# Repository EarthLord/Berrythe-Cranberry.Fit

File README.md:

# Berrythe

## Objective

Create a low-cost alternative for a breathing assistant toy in India by replacing the circuitry of a night light toy. The working is similar these toys in these Amazon US [shopping link 1](https://a.co/d/hcPQM95), [shopping link 2](https://a.co/d/2bBX1N4). Below is a video of the resulting breathing sequence from a retrofit night light toy.

https://github.com/user-attachments/assets/268d343a-7a08-4612-9922-748c09accf75

This open-source project is done for [Cranberry.fit](https://cranberry.fit), a company developing personalized care products to improve menstrual health.

## Repository Content

This repository contains both the hardware and firmware for Berrythe - KiCad PCB design and TI Code Composer Studio Project. The respective hardware and firmware folders contain their documentation as well.

## Specifications of toy

1. Overall, the two functional modes are
    1. Breathing mode of 4, 7, 8
    2. Yellow night light mode
2. This needs to be compatible with the toys below (Amazon India [shopping link 1](https://amzn.in/d/7s0jjhx), [shopping link 2](https://amzn.in/d/guYvsHx))

3. Additional cost for the electronics at quantity of 1000 needs to be less than 300 INR.
4. Battery life
    1. Breathing or Night light mode need needs to be able to run at least for 8 hours on a full charge.
    2. In OFF mode the battery should last at least 6 months.

### Operations of the toy

1. Overall there are three modes for the toy, namely
    1. Power down mode (OFF)
    2. Breathing mode (BREATH)
    3. Yellow night light mode (NIGHT)
2. There is one button for user input interaction, at the bottom of the toy. The two means of interaction with this button is single-press or double-press. Double press isn’t used as it reduces good user experience. 
3. The breathing mode will be on for a time of 10 minutes, following which it’ll power down.
4. The night light mode will be on for a time of 30 minutes, following which it’ll power down.
5. The following will be the flow of operation of the toy

```mermaid
stateDiagram
  direction LR
  [*] --> OFF
  OFF --> BREATH:1-press
  BREATH --> NIGHT:1-press
  BREATH --> OFF:10 min
  NIGHT --> OFF:30 min
  NIGHT --> OFF:1-press
```
6. The breathing mode timing would be as follows to provide an overall 4, 7, 8 breathing exercise. The green and blue color intensity would change as shown below, visually changing linearly. 

| Inhale | Tr | Hold | Tr | Exhale | Tr |
| --- | --- | --- | --- | --- | --- |
| 3.8s | 0.2s | 6.8s | .2s | 7.8s | 0.2s |
7. During the transition time of 0.2s (Tr in above table) the color will shift from previous one to the next one.

## Breathing Technique’s Why and How

### Slow, controlled breathing stimulates the parasympathetic nervous system

This is the part of the nervous system that slows down activity in the body, promotes relaxation, and thus alleviates anxiety and mood changes

### Slows down heart rate, blood pressure, and oxygen consumption

This breathing technique has a low inhale-to-exhale ratio (where you only inhale for 4 seconds and exhale for 8), and requires you to hold your breath. These specific practices may increase your blood oxygen levels and lower your blood pressure. All of which contribute to a less agitated, and more relaxed state.

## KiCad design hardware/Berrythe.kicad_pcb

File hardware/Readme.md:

# Berrythe hardware documentation

This is the hardware setup of V1 of Berrythe. The white PCB is the original PCB from the night light toy. [LP-MSPM0C1104](https://www.ti.com/tool/LP-MSPM0C1104) development kit has a XDS110 debugger and is used to program, debug and log UART to PC.

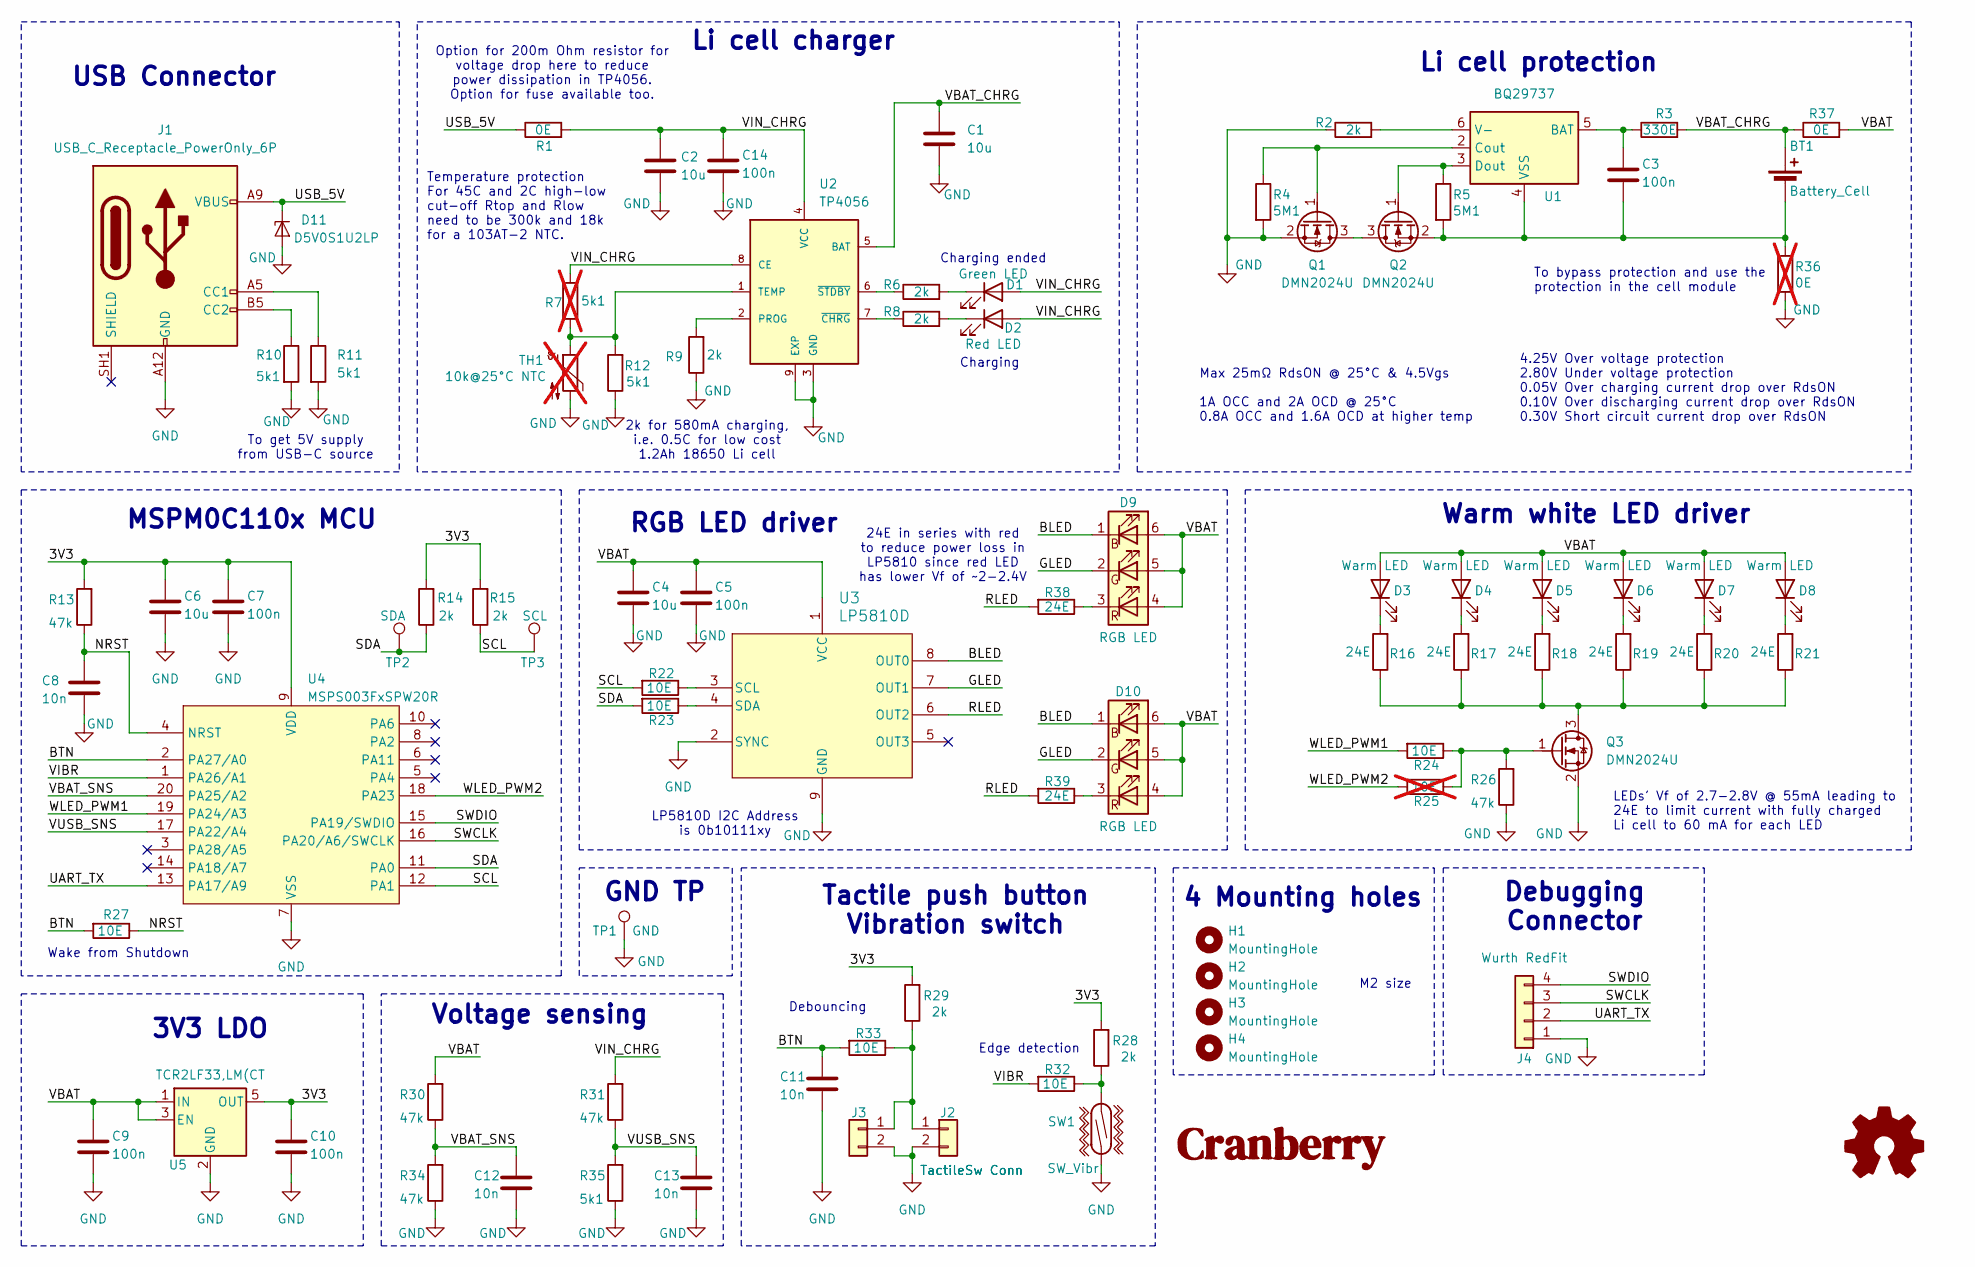
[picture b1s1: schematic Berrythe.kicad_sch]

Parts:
BT1: Battery_Cell; JST_PH_S2B-PH-K_1x02_P2.00mm_Horizontal
C1, C2, C4, C6: 10u; C_0805_2012Metric
C3, C5, C7, C9, C10, C14: 100n; C_0402_1005Metric
C8, C11, C12, C13: 10n; C_0402_1005Metric
D1: Green LED; LED_0603_1608Metric
D2: Red LED; LED_0603_1608Metric
D3, D4, D5, D6, D7, D8: Warm LED; LED_PLCC_2835
D9, D10: RGB LED; LED_RGB_5050-6
D11: D5V0S1U2LP; D_SOD-882D
H1, H2, H3, H4: MountingHole; MountingHole_2.2mm_M2
J1: USB_C_Receptacle_PowerOnly_6P; AMPHENOL_10164359-00011LF
J2: TactileSw Conn; Molex_Pico-Clasp_501331-0207_1x02-1MP_P1.00mm_Vertical
J3: TactileSw Conn; Molex_PicoBlade_53047-0210_1x02_P1.25mm_Vertical
J4: Wurth RedFit; 490107670412_DEBUGGING
Q1, Q2, Q3: DMN2024U; SOT-23
R1: 0E; R_1206_3216Metric
R2, R6, R8, R9, R14, R15, R28, R29: 2k; R_0402_1005Metric
R3: 330E; R_0402_1005Metric
R4, R5: 5M1; R_0402_1005Metric
R7: 5k1; R_0402_1005Metric; not fitted
R10, R11, R12, R35: 5k1; R_0402_1005Metric
R13, R26, R30, R31, R34: 47k; R_0402_1005Metric
R16, R17, R18, R19, R20, R21, R38, R39: 24E; R_0805_2012Metric
R22, R23, R24, R27, R32, R33: 10E; R_0402_1005Metric
R25: 10E; R_0402_1005Metric; not fitted
R36: 0E; R_0402_1005Metric; not fitted
R37: 0E; R_0402_1005Metric
SW1: SW_Vibr; SW-18010P
TH1: 10k@25°C NTC; R_0603_1608Metric; not fitted
TP1: GND; TestPoint_THTPad_D2.5mm_Drill1.2mm
TP2: SDA; TestPoint_Pad_1.0x1.0mm
TP3: SCL; TestPoint_Pad_1.0x1.0mm
U1: BQ29737; WSON-6_1.5x1.5mm_P0.5mm
U2: TP4056; SOIC-8-1EP_3.9x4.9mm_P1.27mm_EP2.41x3.3mm
U3: LP5810D; WSON8-LP5810
U4: MSPS003FxSPW20R; TSSOP-20_4.4x6.5mm_P0.65mm
U5: TCR2LF33,LM(CT; SOT-23-5

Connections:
/3V3: C6.1, C7.1, C10.1, R13.2, R14.2, R15.2, R28.2, R29.2, U4.9 (VDD), U5.5 (OUT)
/BLED: D9.1 (RK), D10.1 (RK), U3.8 (OUT0)
/BTN: C11.1, R27.2, R33.2, U4.2 (PA27/A0)
/GLED: D9.2 (GK), D10.2 (GK), U3.7 (OUT1)
/NRST: C8.1, R13.1, R27.1, U4.4 (NRST)
/RLED: R38.2, R39.2, U3.6 (OUT2)
/SCL: R15.1, R22.2, TP3.1, U4.12 (PA1)
/SDA: R14.1, R23.2, TP2.1, U4.11 (PA0)
/SWCLK: J4.3, U4.16 (PA20/A6/SWCLK)
/SWDIO: J4.4, U4.15 (PA19/SWDIO)
/UART_TX: J4.2, U4.13 (PA17/A9)
/USB_5V: D11.1 (K1), J1.A9 (VBUS), J1.B9 (VBUS), R1.1
/VBAT: C4.1, C5.1, C9.1, D3.2 (A), D4.2 (A), D5.2 (A), D6.2 (A), D7.2 (A), D8.2 (A), D9.4 (BA), D9.5 (GA), D9.6 (RA), D10.4 (BA), D10.5 (GA), D10.6 (RA), R30.2, R37.2, U3.1 (VCC), U5.1 (IN), U5.3 (EN)
/VBAT_CHRG: BT1.2 (+), C1.1, R3.2, R37.1, U2.5 (BAT)
/VBAT_SNS: C12.1, R30.1, R34.2, U4.20 (PA25/A2)
/VIBR: R32.2, U4.1 (PA26/A1)
/VIN_CHRG: C2.1, C14.1, D1.2 (A), D2.2 (A), R1.2, R7.2, R31.2, U2.4 (VCC), U2.8 (CE)
/VUSB_SNS: C13.1, R31.1, R35.2, U4.17 (PA22/A4)
/WLED_PWM1: R24.2, U4.19 (PA24/A3)
/WLED_PWM2: R25.2, U4.18 (PA23)
GND: C1.2, C2.2, C4.2, C5.2, C6.2, C7.2, C8.2, C9.2, C10.2, C11.2, C12.2, C13.2, C14.2, D11.2 (A), J1.A12 (GND), J1.B12 (GND), J2.2, J3.2, J4.1, Q1.2 (S), Q3.2 (S), R2.1, R4.2, R9.1, R10.2, R11.2, R12.1, R26.1, R34.1, R35.1, R36.2, SW1.2, TH1.2, TP1.1, U2.3 (GND), U2.9 (EXP), U3.2 (SYNC), U3.9 (GND), U4.7 (VSS), U5.2 (GND)
unnamed: BT1.1 (-), C3.2, Q2.2 (S), R5.2, R36.1, U1.4 (VSS)
unnamed: D1.1 (K), R6.2
unnamed: D2.1 (K), R8.2
unnamed: D3.1 (K), R16.2
unnamed: D4.1 (K), R17.2
unnamed: D5.1 (K), R18.2
unnamed: D6.1 (K), R19.2
unnamed: D7.1 (K), R20.2
unnamed: D8.1 (K), R21.2
unnamed: D9.3 (BK), R38.1
unnamed: D10.3 (BK), R39.1
unnamed: J1.A5 (CC1), R11.1
unnamed: J1.B5 (CC2), R10.1
unnamed: J2.1, J3.1, R29.1, R33.1
unnamed: Q1.3 (D), Q2.3 (D)
unnamed: Q1.1 (G), R4.1, U1.2 (Cout)
unnamed: Q2.1 (G), R5.1, U1.3 (Dout)
unnamed: Q3.3 (D), R16.1, R17.1, R18.1, R19.1, R20.1, R21.1
unnamed: Q3.1 (G), R24.1, R25.1, R26.2
unnamed: R28.1, R32.1, SW1.1
unnamed: C3.1, R3.1, U1.5 (BAT)
unnamed: R2.2, U1.6 (V-)
unnamed: R9.2, U2.2 (PROG)
unnamed: R7.1, R12.2, TH1.1, U2.1 (TEMP)
unnamed: R8.1, U2.7 (~CHRG)
unnamed: R6.1, U2.6 (~STDBY)
unnamed: R22.1, U3.3 (SCL)
unnamed: R23.1, U3.4 (SDA)

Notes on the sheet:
Charging ended
Debouncing
Option for 200m Ohm resistor for voltage drop here to reduce power dissipation in TP4056. Option for fuse available too.
LEDs' Vf of 2.7-2.8V @ 55mA leading to 24E to limit current with fully charged Li cell to 60 mA for each LED
2k for 580mA charging, i.e. 0.5C for low cost 1.2Ah 18650 Li cell
4.25V Over voltage protection 2.80V Under voltage protection 0.05V Over charging current drop over RdsON 0.10V Over discharging current drop over RdsON 0.30V Short circuit current drop over RdsON
GND TP
Debugging Connector
Tactile push button Vibration switch
4 Mounting holes
Warm white LED driver
Li cell protection
Max 25mΩ RdsON @ 25°C & 4.5Vgs
USB Connector
RGB LED driver
Edge detection
M2 size
Voltage sensing
Li cell charger
Charging
To get 5V supply from USB-C source
To bypass protection and use the protection in the cell module
MSPM0C110x MCU
LP5810D I2C Address is 0b10111xy
24E in series with red to reduce power loss in LP5810 since red LED has lower Vf of ~2-2.4V
Temperature protection For 45C and 2C high-low cut-off Rtop and Rlow need to be 300k and 18k for a 103AT-2 NTC.
3V3 LDO
1A OCC and 2A OCD @ 25°C 0.8A OCC and 1.6A OCD at higher temp
Wake from Shutdown

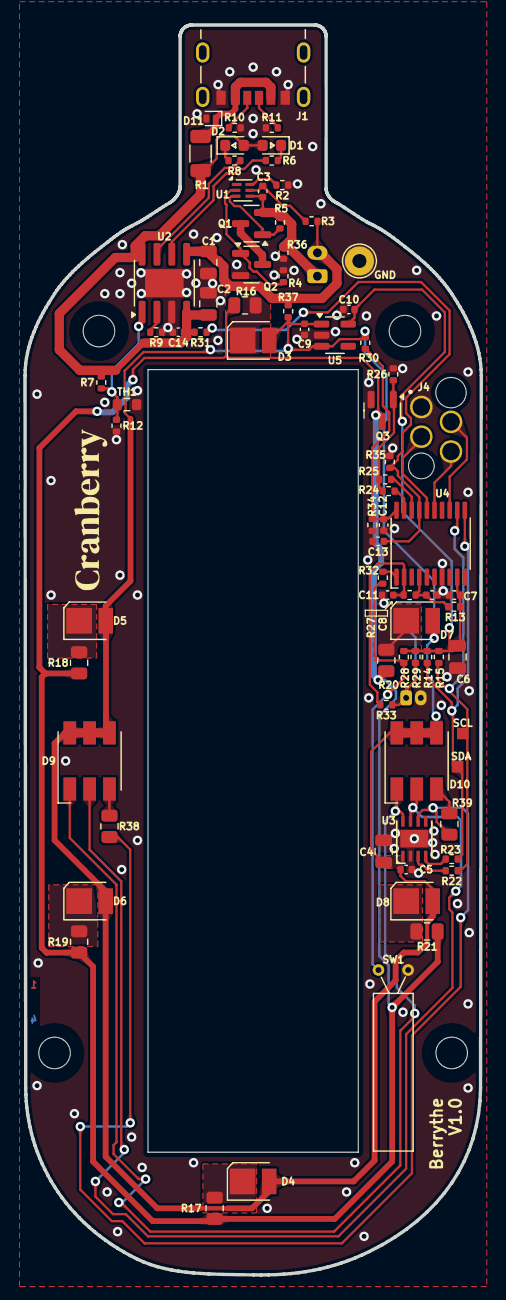
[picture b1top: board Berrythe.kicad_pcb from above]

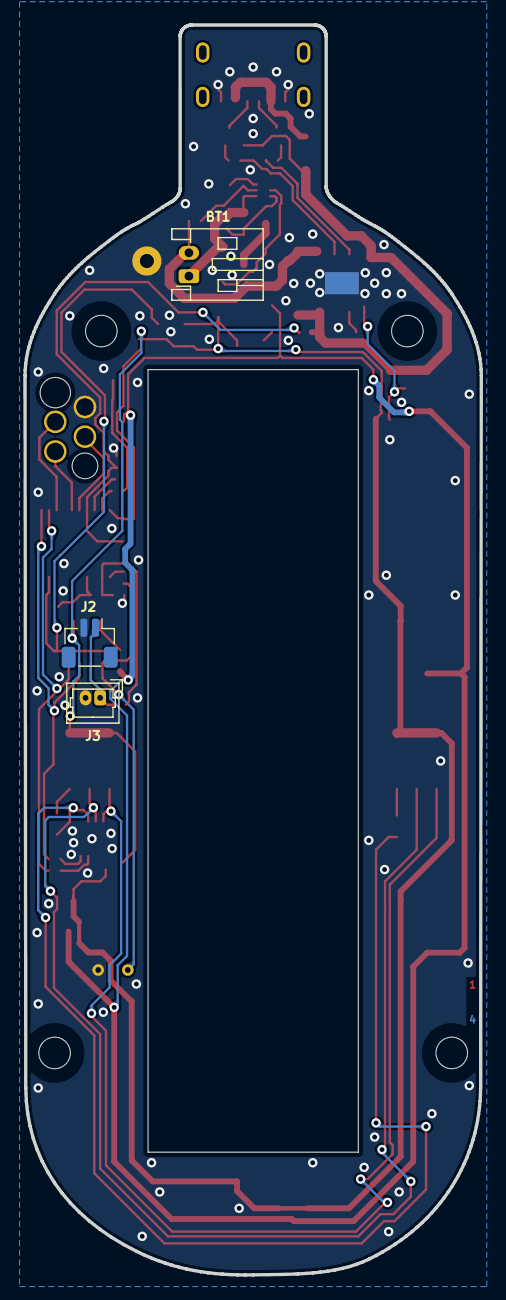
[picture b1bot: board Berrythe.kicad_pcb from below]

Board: 4 copper layers, 39.1 x 107.0 mm, 86 parts (3 on the bottom side), 49 nets.

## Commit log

2025-01-22 Initial commit containing ReadMe and gitignore
2025-01-22 KiCad PCB design for V1 of Berrythe hardware
2025-01-22 Code Composer studio project of Berrythe firmware
    Works as per requirement.
    Only pending issue is blockiness in blue light dimming.
2025-01-22 Added basic info of the hardware setup in a readme.md file
2025-01-29 Update readme with video of the final 4-7-8 sequence from toy
2025-01-29 Update README.md
    Video isn't showing properly
2025-01-29 Update README.md with video link using drag-drop
2025-01-29 Remove 4-7-8 sequence as it is directly in Github link
2025-01-29 Update to MSPM0C1104 from MSPM0C11003 to check different memory intensive algo.
    Update SDK used
2025-01-29 Add debug config for MSPM0C1104
2025-01-29 Add BSD 3-clause license
2025-01-29 Add BSD 3 clause license file
2025-01-29 Rename LP5810 start sequence functiuon to not use 478 in the name
2025-01-29 Don't enable exponential curve brighness control
2025-01-29 Battery state check value is 2's power in ms
2025-01-29 Batt state enables use of ADC offset
2025-01-29 Breathe mode uses another sequence for blue exhale
    and uses 16 bit with gamma correction to reduce blockiness in fade in or out
2025-01-29 Correct some license issues and update test for reset issues
2025-02-17 Updated state machine based on Graphviz code
2025-02-17 Revert to older state machine for initial page to have simpler overview
2025-02-17 Mention the documentation available for hardware and firmware
2025-02-17 Initial version of the firmware readme. Button sensing is left to be explained.
2025-02-17 Add Graphviz Dot source in comment for the state machine and flow charts.
2025-02-18 Update README.md
    Use state machine of Mermaid inline
2025-02-18 Update Readme.md
    Update state machine and flow chart images based on Mermaid based description in Markdown
2025-02-18 Removed flow charts and state machine images - not needed now
2025-02-21 Remove te graphviz code in comment to generate diagram
2025-02-21 Add block diagram of test jig
2025-02-27 Update Readme.md
    Added color to some lines and changed 5V supply to one unit
2025-03-25 Create test jig 3D model for printing
